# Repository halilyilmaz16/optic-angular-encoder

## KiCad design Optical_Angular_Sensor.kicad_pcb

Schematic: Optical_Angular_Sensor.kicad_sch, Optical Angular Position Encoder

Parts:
C1: 220uF 25V; CP_Radial_D8.0mm_P3.50mm
C2, C3: 4.7pF; C_Disc_D5.0mm_W2.5mm_P5.00mm
C4, C5, C6, C7, C8, C9, C10, C11, C12, C13, C14, C15, C16, C17, C18, C19, C20, C21, C22, C23, C24, C25, C26, C27, C28, C29, C30, C31, C32, C33, C34, C35, C36, C37, C38: 100nF; C_Disc_D5.0mm_W2.5mm_P5.00mm
C100: 1uF; C_Disc_D5.0mm_W2.5mm_P5.00mm
DS1, DS2, DS3: SA39-11EWA; Sx39-1xxxxx; MPN SA39-11EWA
J1: +5V IN; TerminalBlock_Phoenix_MKDS-1,5-2_1x02_P5.00mm_Horizontal
J2: IR LEDs; PinHeader_1x04_P2.54mm_Vertical
J3: BPW41N x2 (K=PD_x, A=GND); PinHeader_1x04_P2.54mm_Vertical
J4: TEST / EXT; PinHeader_1x06_P2.54mm_Vertical
R1, R2: 220; R_Axial_DIN0207_L6.3mm_D2.5mm_P7.62mm_Horizontal
R3, R4: 200k; R_Axial_DIN0207_L6.3mm_D2.5mm_P7.62mm_Horizontal
R5, R9: 470k; R_Axial_DIN0207_L6.3mm_D2.5mm_P7.62mm_Horizontal
R6, R7, R8, R10, R11, R12, R100: 10k; R_Axial_DIN0207_L6.3mm_D2.5mm_P7.62mm_Horizontal
R13, R14: 680; R_Axial_DIN0207_L6.3mm_D2.5mm_P7.62mm_Horizontal
R15, R16, R17, R18, R19, R20, R21, R22, R23, R24, R25, R26, R27, R28, R29, R30, R31, R32, R33, R34, R35: 330; R_Axial_DIN0207_L6.3mm_D2.5mm_P7.62mm_Horizontal
SW1: RESET; SW_PUSH_6mm
U1: LM358P; DIP-8_W7.62mm; MPN LM358P
U2: LM393P; DIP-8_W7.62mm; MPN LM393P
U3, U9, U10, U13, U15, U17, U20, U21: 74HC157; DIP-16_W7.62mm; MPN SN74HC157N
U4, U5, U6: 74LS47; DIP-16_W7.62mm; MPN SN74LS47N
U7, U8: CD4029B; DIP-16_W7.62mm; MPN CD4029BE
U11, U12, U14, U16, U18, U19: CD4063B; DIP-16_W7.62mm; MPN CD4063BE
U22, U23: 74HC74; DIP-14_W7.62mm; MPN SN74HC74N
U24, U25, U26, U27, U28: CD4081B; DIP-14_W7.62mm; MPN CD4081BE
U29, U30: CD4071B; DIP-14_W7.62mm; MPN CD4071BE
U31, U32: 74HC04; DIP-14_W7.62mm; MPN SN74HC04N
U33: 74HC86; DIP-14_W7.62mm; MPN SN74HC86N
U34, U35: 74HC21; DIP-14_W7.62mm; MPN SN74HC21N

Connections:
+5V: C1.1, C4.1, C5.1, C6.1, C7.1, C8.1, C9.1, C10.1, C11.1, C12.1, C13.1, C14.1, C15.1, C16.1, C17.1, C18.1, C19.1, C20.1, C21.1, C22.1, C23.1, C24.1, C25.1, C26.1, C27.1, C28.1, C29.1, C30.1, C31.1, C32.1, C33.1, C34.1, C35.1, C36.1, C37.1, C38.1, C100.1, DS1.3 (CA), DS1.8 (CA), DS2.3 (CA), DS2.8 (CA), DS3.3 (CA), DS3.8 (CA), J1.1, J4.1, R6.1, R7.1, R10.1, R11.1, R13.1, R14.1, SW1.1, U1.8 (V+), U2.8 (V+), U3.16 (VCC), U4.3 (LT), U4.5 (RBI), U4.16 (VCC), U5.3 (LT), U5.5 (RBI), U5.16 (VCC), U6.3 (LT), U6.5 (RBI), U6.16 (VCC), U7.9 (B/D), U7.16 (VDD), U8.9 (B/D), U8.16 (VDD), U9.2 (I0a), U9.5 (I0b), U9.11 (I0c), U9.14 (I0d), U9.16 (VCC), U10.2 (I0a), U10.5 (I0b), U10.11 (I0c), U10.14 (I0d), U10.16 (VCC), U11.3 (Ia=b), U11.11 (B1), U11.14 (B2), U11.16 (VCC), U12.3 (Ia=b), U12.9 (B0), U12.11 (B1), U12.16 (VCC), U13.2 (I0a), U13.5 (I0b), U13.11 (I0c), U13.14 (I0d), U13.16 (VCC), U14.1 (B3), U14.3 (Ia=b), U14.11 (B1), U14.16 (VCC), U15.16 (VCC), U16.1 (B3), U16.3 (Ia=b), U16.9 (B0), U16.11 (B1), U16.14 (B2), U16.16 (VCC), U17.2 (I0a), U17.3 (I1a), U17.5 (I0b), U17.11 (I0c), U17.13 (I1d), U17.14 (I0d), U17.16 (VCC), U18.3 (Ia=b), U18.16 (VCC), U19.3 (Ia=b), U19.16 (VCC), U20.2 (I0a), U20.5 (I0b), U20.6 (I1b), U20.10 (I1c), U20.11 (I0c), U20.14 (I0d), U20.16 (VCC), U21.2 (I0a), U21.3 (I1a), U21.5 (I0b), U21.6 (I1b), U21.11 (I0c), U21.14 (I0d), U21.16 (VCC), U22.1 (~R), U22.4 (~S), U22.10 (~S), U22.13 (~R), U22.14 (VCC), U23.1 (~R), U23.4 (~S), U23.10 (~S), U23.13 (~R), U23.14 (VCC), U24.14 (VDD), U25.14 (VDD), U26.14 (VDD), U27.14 (VDD), U28.14 (VDD), U29.14 (VDD), U30.14 (VDD), U31.5, U31.14 (VCC), U32.14 (VCC), U33.14 (VCC), U34.14 (VCC), U35.14 (VCC)
/CLK_HUND: U3.9 (Zc), U8.15 (CK)
/CLK_ONES: U3.4 (Za), U23.11 (C)
/CLK_TENS: U3.7 (Zb), U7.15 (CK)
/DIR_CHANGED: U25.9, U25.13, U33.3
/DIR_PREV: U22.9 (Q), U24.13, U32.1, U33.1
/DIR_RAW: U15.2 (I0a), U22.5 (Q)
/EQ_TENS10: U3.10 (I1c), U9.1 (S), U14.6 (Oa=b), U29.1
/EQ_TENS15: U3.11 (I0c), U16.6 (Oa=b), U17.1 (S), U30.8
/HUND_A: U6.7 (A), U8.6 (Q1), U12.10 (A0), U19.10 (A0)
/HUND_B: U6.1 (B), U8.11 (Q2), U12.12 (A1), U19.12 (A1)
/HUND_C: U6.2 (C), U8.14 (Q3), U12.13 (A2), U19.13 (A2)
/HUND_D: U6.6 (D), U8.2 (Q4), U12.15 (A3), U19.15 (A3)
/JH_54_U10: U10.4 (Za), U27.12
/JH_54_U21: U21.4 (Za), U27.13
/JH_55_U10: U10.7 (Zb), U28.1
/JH_55_U21: U21.7 (Zb), U28.2
/JH_56_U10: U10.9 (Zc), U28.5
/JH_56_U21: U21.9 (Zc), U28.6
/JH_57_U10: U10.12 (Zd), U28.8
/JH_57_U21: U21.12 (Zd), U28.9
/JT_42_U9: U9.4 (Za), U34.1
/JT_42_U13: U13.4 (Za), U34.2
/JT_42_U17: U17.4 (Za), U34.4
/JT_42_U20: U20.4 (Za), U34.5
/JT_43_U9: U9.7 (Zb), U34.9
/JT_43_U13: U13.7 (Zb), U34.10
/JT_43_U17: U17.7 (Zb), U34.12
/JT_43_U20: U20.7 (Zb), U34.13
/JT_44_U9: U9.9 (Zc), U35.1
/JT_44_U13: U13.9 (Zc), U35.2
/JT_44_U17: U17.9 (Zc), U35.4
/JT_44_U20: U20.9 (Zc), U35.5
/JT_45_U9: U9.12 (Zd), U35.9
/JT_45_U13: U13.12 (Zd), U35.10
/JT_45_U17: U17.12 (Zd), U35.12
/JT_45_U20: U20.12 (Zd), U35.13
/LED_A: J2.1, R13.2
/LED_B: J2.3, R14.2
/N00001: R15.1, U4.13 (a)
/N00003: R16.1, U4.12 (b)
/N00004: R17.1, U4.11 (c)
/N00005: R18.1, U4.10 (d)
/N00007: R19.1, U4.9 (e)
/N00009: R20.1, U4.15 (f)
/N00010: R21.1, U4.14 (g)
/N00014: R22.1, U5.13 (a)
/N00016: R23.1, U5.12 (b)
/N00018: R24.1, U5.11 (c)
/N00020: R25.1, U5.10 (d)
/N00022: R26.1, U5.9 (e)
/N00024: R27.1, U5.15 (f)
/N00025: R28.1, U5.14 (g)
/N00029: R29.1, U6.13 (a)
/N00031: R30.1, U6.12 (b)
/N00033: R31.1, U6.11 (c)
/N00035: R32.1, U6.10 (d)
/N00037: R33.1, U6.9 (e)
/N00038: R34.1, U6.15 (f)
/N00039: R35.1, U6.14 (g)
/N00042: U7.4 (J1), U34.6
/N00043: U7.12 (J2), U34.8
/N00044: U7.13 (J3), U35.6
/N00045: U7.3 (J4), U35.8
/N00054: U8.4 (J1), U27.11
/N00055: U8.12 (J2), U28.3
/N00056: U8.13 (J3), U28.4
/N00057: U8.3 (J4), U28.10
/N00092: U3.2 (I0a), U31.2
/N00094: U3.5 (I0b), U25.4
/N00095: U3.6 (I1b), U25.3
/N00104: U24.5, U25.2, U27.5, U31.4
/N00130: U11.6 (Oa=b), U24.1
/N00137: U12.6 (Oa=b), U24.2
/N00141: U24.3, U24.6
/N00148: U26.1, U29.3
/N00173: U25.1, U31.8
/N00174: U25.5, U31.12
/N00177: U15.3 (I1a), U23.5 (Q)
/N00191: U15.1 (S), U31.6
/N00197: U26.11, U29.5
/N00198: U24.4, U26.12
/N00199: U24.12, U25.10
/N00200: U25.12, U31.10
/N00201: U24.8, U25.11
/N00204: U23.8 (~Q), U23.12 (D)
/N00210: U24.9, U32.2
/N00211: U24.10, U31.9
/N00212: U24.11, U31.13
/N00213: U26.3, U30.1
/N00214: U29.8, U30.3
/N00215: U26.4, U30.5
/N00216: U29.12, U30.4
/N00231: U26.8, U30.10
/N00232: U26.9, U32.4
/N00233: U26.10, U30.2
/N00238: U18.6 (Oa=b), U27.1
/N00243: U19.6 (Oa=b), U27.2
/N00247: U27.3, U27.6
/N00248: U27.4, U27.8
/N00263: U27.9, U32.6
/ONES_Q: U4.2 (C), U4.7 (A), U23.9 (Q), U25.6, U25.8, U31.3, U31.11
/PD_A: J3.2, R1.1
/PD_B: J3.4, R2.1
/PE_HUND: U8.1 (PE), U29.11
/PE_TENS: U7.1 (PE), U29.10
/PHASE_A: J4.2, R5.2, R6.2, U2.1, U3.3 (I1a), U22.2 (D), U22.11 (C), U23.2 (D), U31.1
/PHASE_B: J4.3, R9.2, R10.2, U2.7
/RESET: C100.2, R100.1, SW1.2, U29.6, U29.9, U29.13
/SEG_HUND_A: DS3.10 (A), R29.2
/SEG_HUND_B: DS3.9 (B), R30.2
/SEG_HUND_C: DS3.7 (C), R31.2
/SEG_HUND_D: DS3.5 (D), R32.2
/SEG_HUND_E: DS3.4 (E), R33.2
/SEG_HUND_F: DS3.2 (F), R34.2
/SEG_HUND_G: DS3.1 (G), R35.2
/SEG_ONES_A: DS1.10 (A), R15.2
/SEG_ONES_B: DS1.9 (B), R16.2
/SEG_ONES_C: DS1.7 (C), R17.2
/SEG_ONES_D: DS1.5 (D), R18.2
/SEG_ONES_E: DS1.4 (E), R19.2
/SEG_ONES_F: DS1.2 (F), R20.2
/SEG_ONES_G: DS1.1 (G), R21.2
/SEG_TENS_A: DS2.10 (A), R22.2
/SEG_TENS_B: DS2.9 (B), R23.2
/SEG_TENS_C: DS2.7 (C), R24.2
/SEG_TENS_D: DS2.5 (D), R25.2
/SEG_TENS_E: DS2.4 (E), R26.2
/SEG_TENS_F: DS2.2 (F), R27.2
/SEG_TENS_G: DS2.1 (G), R28.2
/SEL_HI: U10.1 (S), U13.1 (S), U26.5, U29.2, U29.4
/TENS_A: U5.7 (A), U7.6 (Q1), U11.10 (A0), U14.10 (A0), U16.10 (A0), U18.10 (A0)
/TENS_B: U5.1 (B), U7.11 (Q2), U11.12 (A1), U14.12 (A1), U16.12 (A1), U18.12 (A1)
/TENS_C: U5.2 (C), U7.14 (Q3), U11.13 (A2), U14.13 (A2), U16.13 (A2), U18.13 (A2)
/TENS_D: U5.6 (D), U7.2 (Q4), U11.15 (A3), U14.15 (A3), U16.15 (A3), U18.15 (A3)
/TIA_A: C2.2, J4.4, R3.2, U1.1, U2.2 (-)
/TIA_A_IN: C2.1, R1.2, R3.1, U1.2 (-)
/TIA_B: C3.2, J4.5, R4.2, U1.7, U2.6 (-)
/TIA_B_IN: C3.1, R2.2, R4.1, U1.6 (-)
/UP_DN: U3.1 (S), U7.10 (U/D), U8.10 (U/D), U15.4 (Za), U22.12 (D), U26.2, U26.6, U26.13, U32.3, U32.5, U33.2
/VREF_A: R5.1, R7.2, R8.1, U2.3 (+)
/VREF_B: R9.1, R11.2, R12.1, U2.5 (+)
/WRAP_DN: U20.1 (S), U21.1 (S), U27.10, U30.6, U30.9
GND: C1.2, C4.2, C5.2, C6.2, C7.2, C8.2, C9.2, C10.2, C11.2, C12.2, C13.2, C14.2, C15.2, C16.2, C17.2, C18.2, C19.2, C20.2, C21.2, C22.2, C23.2, C24.2, C25.2, C26.2, C27.2, C28.2, C29.2, C30.2, C31.2, C32.2, C33.2, C34.2, C35.2, C36.2, C37.2, C38.2, J1.2, J2.2, J2.4, J3.1, J3.3, J4.6, R8.2, R12.2, R100.2, U1.3 (+), U1.4 (V-), U1.5 (+), U2.4 (V-), U3.8 (GND), U3.13 (I1d), U3.14 (I0d), U3.15 (E), U4.1 (B), U4.6 (D), U4.8 (GND), U5.8 (GND), U6.8 (GND), U7.5 (Cin), U7.8 (VSS), U8.5 (Cin), U8.8 (VSS), U9.3 (I1a), U9.6 (I1b), U9.8 (GND), U9.10 (I1c), U9.13 (I1d), U9.15 (E), U10.3 (I1a), U10.6 (I1b), U10.8 (GND), U10.10 (I1c), U10.13 (I1d), U10.15 (E), U11.1 (B3), U11.2 (Ia<b), U11.4 (Ia>b), U11.8 (GND), U11.9 (B0), U12.1 (B3), U12.2 (Ia<b), U12.4 (Ia>b), U12.8 (GND), U12.14 (B2), U13.3 (I1a), U13.6 (I1b), U13.8 (GND), U13.10 (I1c), U13.13 (I1d), U13.15 (E), U14.2 (Ia<b), U14.4 (Ia>b), U14.8 (GND), U14.9 (B0), U14.14 (B2), U15.5 (I0b), U15.6 (I1b), U15.8 (GND), U15.10 (I1c), U15.11 (I0c), U15.13 (I1d), U15.14 (I0d), U15.15 (E), U16.2 (Ia<b), U16.4 (Ia>b), U16.8 (GND), U17.6 (I1b), U17.8 (GND), U17.10 (I1c), U17.15 (E), U18.1 (B3), U18.2 (Ia<b), U18.4 (Ia>b), U18.8 (GND), U18.9 (B0), U18.11 (B1), U18.14 (B2), U19.1 (B3), U19.2 (Ia<b), U19.4 (Ia>b), U19.8 (GND), U19.9 (B0), U19.11 (B1), U19.14 (B2), U20.3 (I1a), U20.8 (GND), U20.13 (I1d), U20.15 (E), U21.8 (GND), U21.10 (I1c), U21.13 (I1d), U21.15 (E), U22.7 (GND), U23.3 (C), U23.7 (GND), U24.7 (VSS), U25.7 (VSS), U26.7 (VSS), U27.7 (VSS), U28.7 (VSS), U28.12, U28.13, U29.7 (VSS), U30.7 (VSS), U30.12, U30.13, U31.7 (GND), U32.7 (GND), U32.9, U32.11, U32.13, U33.4, U33.5, U33.7 (GND), U33.9, U33.10, U33.12, U33.13, U34.7 (GND), U35.7 (GND)

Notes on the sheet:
1 OPTICAL FRONT END: LEDs, PHOTODIODES (zero-bias), TIA (LM358) + SCHMITT (LM393)
8 RESET (report block 12): push-button + power-on RC -> loads 000
Power-on: C100 pulls RESET high ~10 ms (R100 x C100). RESET high -> PE of both CD4029 via OR gates, muxes load 000.
2 DIRECTION DETECTION & GLITCH BLOCKER
3 TENS / HUNDREDS COUNTERS (CD4029)
4 BOUNDARY COMPARATORS (CD4063)
5 PRESET MULTIPLEXERS + JAM AND (wired-AND made explicit)
6 BCD -> 7-SEGMENT (74LS47, 330R, common-anode displays)
7 SUPPLY: IC power units + 100 nF decoupling (one per IC, placed at its VCC pin on the PCB)
Rev C: counter/display logic from Proteus netlist Counter_gurup2 (SDF). See DESIGN_REVIEW.md for the Proteus->KiCad reference table and every deviation (wired-AND jam lines, floating inputs tied, isolated U19/U20 block removed).

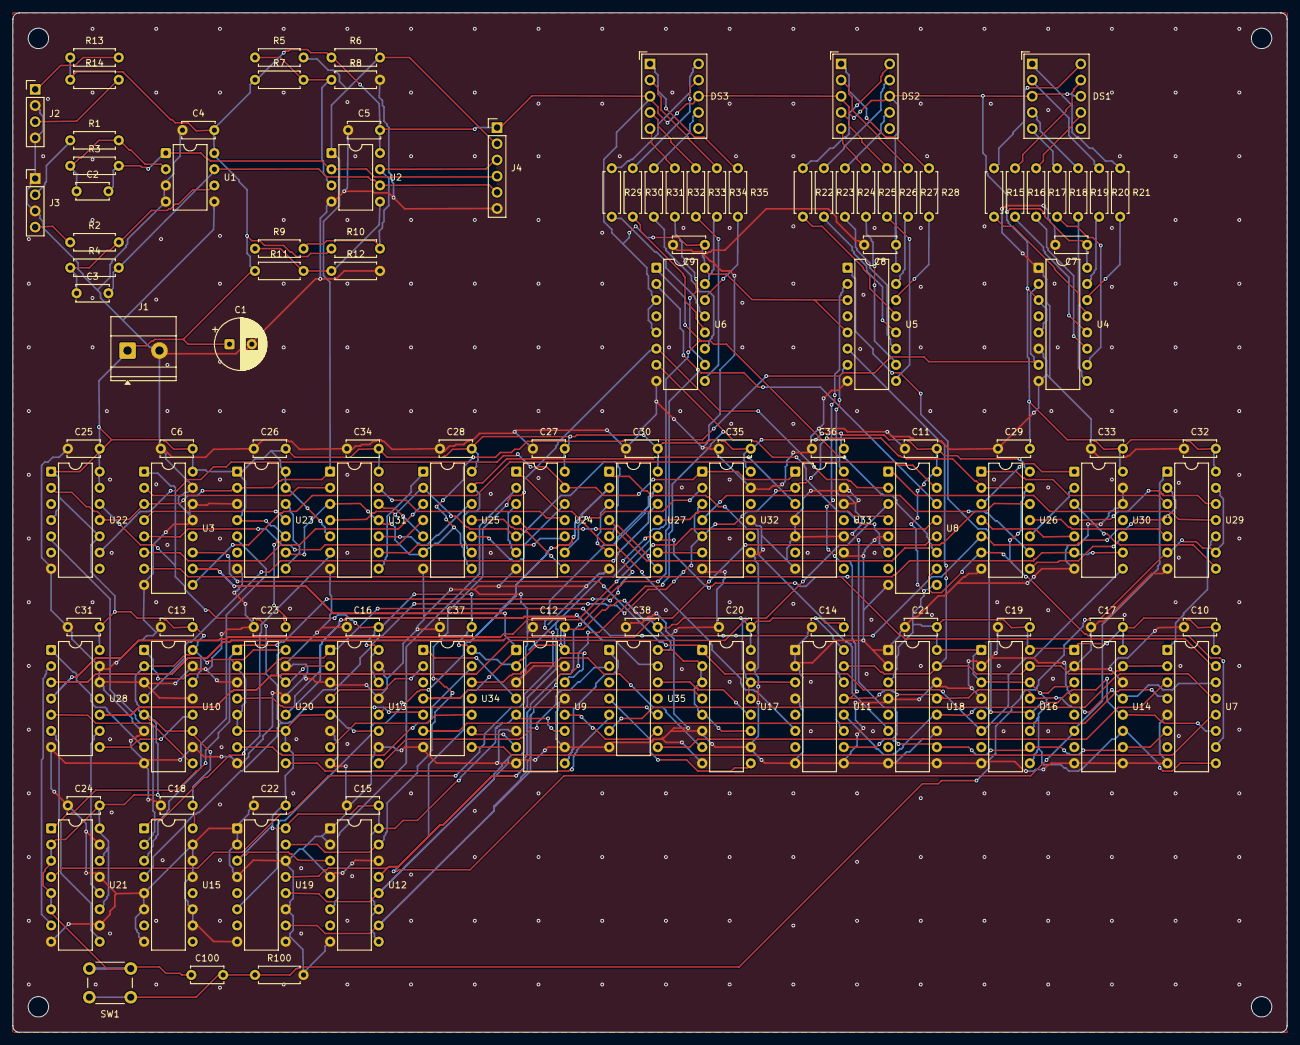
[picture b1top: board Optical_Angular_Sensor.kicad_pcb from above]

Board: 2 copper layers, 200.0 x 160.0 mm, 122 parts (0 on the bottom side), 144 nets.

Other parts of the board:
H1, H2, H3, H4: MountingHole_3.2mm_M3

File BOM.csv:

"Reference","Value","Footprint","MPN","Qty"
"C1","220uF 25V","Capacitor_THT:CP_Radial_D8.0mm_P3.50mm","","1"
"C2,C3","4.7pF","Capacitor_THT:C_Disc_D5.0mm_W2.5mm_P5.00mm","","2"
"C4-C38","100nF","Capacitor_THT:C_Disc_D5.0mm_W2.5mm_P5.00mm","","35"
"C100","1uF","Capacitor_THT:C_Disc_D5.0mm_W2.5mm_P5.00mm","","1"
"DS1-DS3","SA39-11EWA","Display_7Segment:Sx39-1xxxxx","SA39-11EWA","3"
"J1","+5V IN","TerminalBlock_Phoenix:TerminalBlock_Phoenix_MKDS-1,5-2_1x02_P5.00mm_Horizontal","","1"
"J2","IR LEDs","Connector_PinHeader_2.54mm:PinHeader_1x04_P2.54mm_Vertical","","1"
"J3","BPW41N x2 (K=PD_x, A=GND)","Connector_PinHeader_2.54mm:PinHeader_1x04_P2.54mm_Vertical","","1"
"J4","TEST / EXT","Connector_PinHeader_2.54mm:PinHeader_1x06_P2.54mm_Vertical","","1"
"R1,R2","220","Resistor_THT:R_Axial_DIN0207_L6.3mm_D2.5mm_P7.62mm_Horizontal","","2"
"R3,R4","200k","Resistor_THT:R_Axial_DIN0207_L6.3mm_D2.5mm_P7.62mm_Horizontal","","2"
"R5,R9","470k","Resistor_THT:R_Axial_DIN0207_L6.3mm_D2.5mm_P7.62mm_Horizontal","","2"
"R6-R8,R10-R12,R100","10k","Resistor_THT:R_Axial_DIN0207_L6.3mm_D2.5mm_P7.62mm_Horizontal","","7"
"R13,R14","680","Resistor_THT:R_Axial_DIN0207_L6.3mm_D2.5mm_P7.62mm_Horizontal","","2"
"R15-R35","330","Resistor_THT:R_Axial_DIN0207_L6.3mm_D2.5mm_P7.62mm_Horizontal","","21"
"SW1","RESET","Button_Switch_THT:SW_PUSH_6mm","","1"
"U1","LM358P","Package_DIP:DIP-8_W7.62mm","LM358P","1"
"U2","LM393P","Package_DIP:DIP-8_W7.62mm","LM393P","1"
"U3,U9,U10,U13,U15,U17,U20,U21","74HC157","Package_DIP:DIP-16_W7.62mm","SN74HC157N","8"
"U4-U6","74LS47","Package_DIP:DIP-16_W7.62mm","SN74LS47N","3"
"U7,U8","CD4029B","Package_DIP:DIP-16_W7.62mm","CD4029BE","2"
"U11,U12,U14,U16,U18,U19","CD4063B","Package_DIP:DIP-16_W7.62mm","CD4063BE","6"
"U22,U23","74HC74","Package_DIP:DIP-14_W7.62mm","SN74HC74N","2"
"U24-U28","CD4081B","Package_DIP:DIP-14_W7.62mm","CD4081BE","5"
"U29,U30","CD4071B","Package_DIP:DIP-14_W7.62mm","CD4071BE","2"
"U31,U32","74HC04","Package_DIP:DIP-14_W7.62mm","SN74HC04N","2"
"U33","74HC86","Package_DIP:DIP-14_W7.62mm","SN74HC86N","1"
"U34,U35","74HC21","Package_DIP:DIP-14_W7.62mm","SN74HC21N","2"
